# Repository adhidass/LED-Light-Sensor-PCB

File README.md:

# First KiCad Project
## Light sensor that has adjustable threshold using potentiometer, uses LED as the photodiode and LMC6482 op-amp

[Schematic (PDF)](Docs/LED%20Light%20Sensor.pdf)

## How it works
1. Sensor: Light makes the photodiode leak a tiny current.
2. Amplifier (U1A): turns that current into a voltage, centered on a 1.65 V reference.
3. Comparator (U1B): compares the sensor voltage against the potentiometer's level. The output goes high or low depending on which is larger.

Powered by 3.3 V through a 3-pin header (3.3 V, Vout, GND).

## Status
Designed in KiCad, DRC clean. Not yet fabricated or tested.

## Files
- `Hardware/`: KiCad project files
- `Docs/`: schematic PDF and board image
- `LED Light Sensor.zip`: Gerber and drill files for manufacturing

## Credit: 
A step by step tutorial by @inkedbhav on tiktok. Assisted by Claude AI (Sonnet 5.5)

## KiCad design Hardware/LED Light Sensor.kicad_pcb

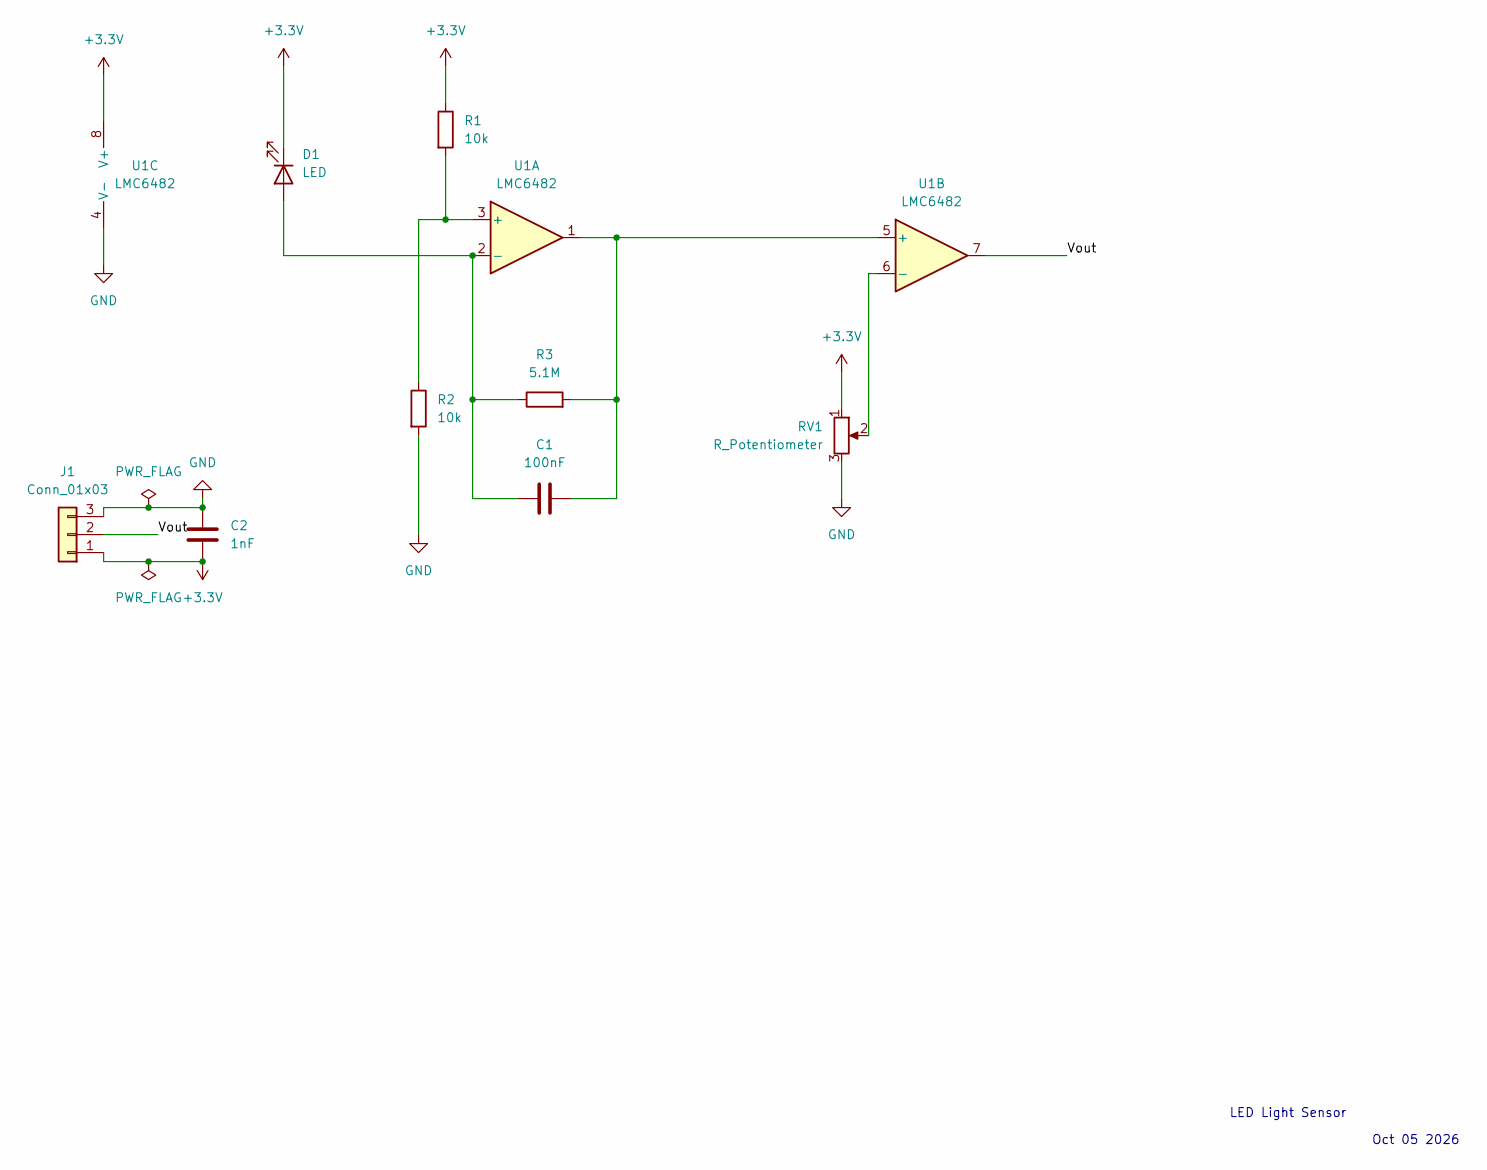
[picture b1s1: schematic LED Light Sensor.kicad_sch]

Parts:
C1: 100nF; C_0805_2012Metric
C2: 1nF; C_0805_2012Metric
D1: LED; LED_D5.0mm
J1: Conn_01x03; PinHeader_1x03_P2.54mm_Vertical
R1, R2: 10k; R_0805_2012Metric
R3: 5.1M; R_0805_2012Metric
RV1: R_Potentiometer; Potentiometer_Bourns_3296W_Vertical
U1: LMC6482; DIP-8_W7.62mm

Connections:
+3.3V: C2.2, D1.1 (K), J1.1, R1.1, RV1.1, U1.8 (V+)
/Vout: J1.2, U1.7
GND: C2.1, J1.3, R2.2, RV1.3, U1.4 (V-)
unnamed: C1.1, D1.2 (A), R3.1, U1.2 (-)
unnamed: R1.2, R2.1, U1.3 (+)
unnamed: C1.2, R3.2, U1.1, U1.5 (+)
unnamed: RV1.2, U1.6 (-)

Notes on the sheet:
LED Light Sensor
Oct 05 2026

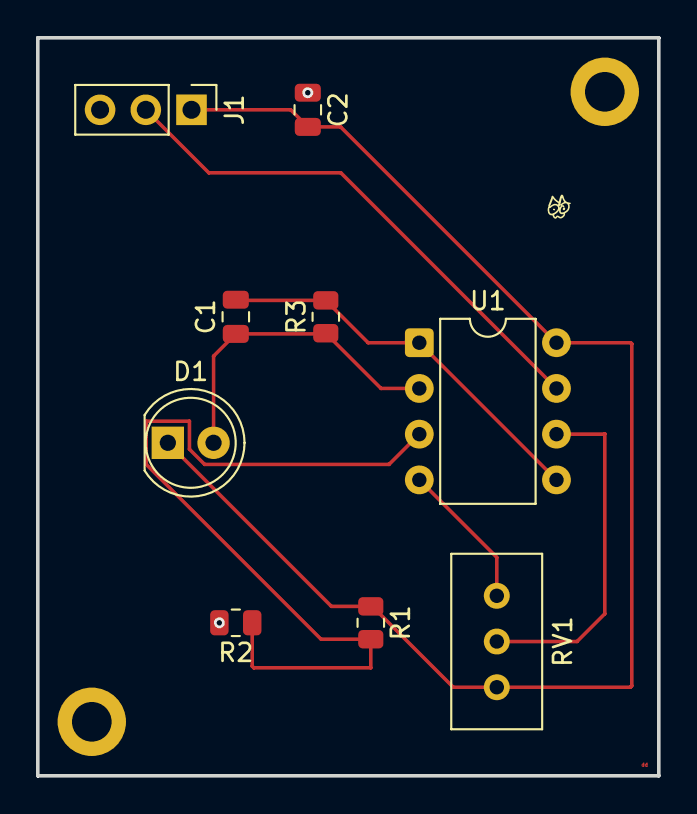
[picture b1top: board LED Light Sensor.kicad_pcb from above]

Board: 2 copper layers, 34.5 x 41.0 mm, 9 parts (0 on the bottom side), 7 nets.
